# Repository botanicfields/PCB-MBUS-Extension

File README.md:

# PCB-MBUS-Extension
a Printed Circuit Board of M-Bus Extension for M5Stack

# M-Busエクステンション基板キット
M5Stackの外にM-Busモジュールを接続するエクステンション基板のキットです。M5Stack用BUSモジュールに取り付けて使用します。
- M5StackのLCDやボタンを使いながら、M-Busモジュールの試験や調整ができます。
- プロービング用のピンソケットからジャンパーワイヤーでM-Bus信号を観測できます。
- ボトムに出ていないM-Bus信号を観測できます。

## 委託販売（スイッチサイエンス）
https://www.switch-science.com/catalog/7371/

## 内容物
- プリント基板 ×1
- M-Busピンソケット(M5Stack純正品) ×1
- ピンソケット(一般用15ピン2列) ×1
- ピンソケット(一般用L型15ピン2列) ×1

※ M5Stack用BUSモジュールは付属しません。別途ご用意ください。

## ご注意
- 組み立てには、はんだ付け（表面実装を含む）が必要です。
- M-Bus信号へのノイズ混入により動作が不安定になる場合があります。信号には手を触れない様にしてください。
- M5Stack用BUSモジュールを含め基板パターンの電流容量が不足する可能性があります。GND, 5V, 3.3V, BAT, HPWRなど、必要に応じてディスクリートワイヤで補強してください。
- 取り扱い説明書はありません。

## 使用方法
- M5Stack用BUSモジュールについて、モジュール付属のL型ピンヘッダをはんだ付けし、モールド側面の開口部をカッター等で切り取ります。
- M5Stack用BUSモジュールに、組み立てたM-Busエクステンション基板を、**裏表が逆になるように取り付けます**。
- 本来、M5Stackの裏面側にあるM-Busモジュールが、エクステンション基板では表面を向きます。

## 使用例
RTCモジュールのCLKO信号を、M-Busエクステンション基板のGPIO36から取り出して周波数カウンタで観測しながら、RTCモジュールの水晶発振子のトリマを調整しています。M5StackのLCDも同時に見ることができます。

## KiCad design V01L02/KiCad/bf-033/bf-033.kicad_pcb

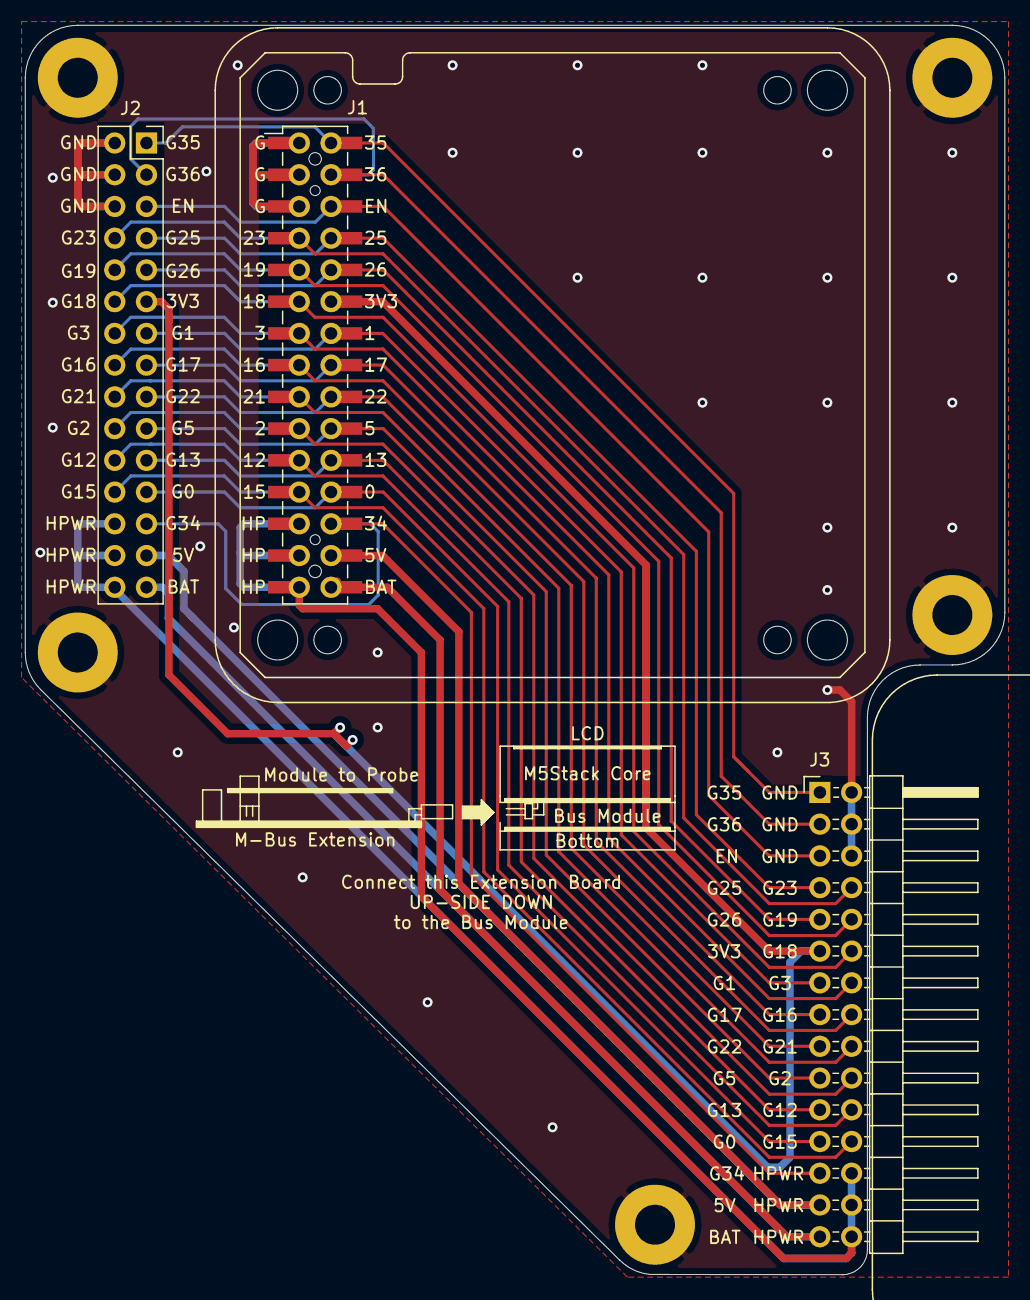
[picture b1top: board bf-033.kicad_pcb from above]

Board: 2 copper layers, 78.4 x 100.0 mm, 11 parts (0 on the bottom side), 26 nets.

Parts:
H1, H2, H3, H4: MountingHole; BF@MountingHole_3.2mm_M3
H5, H6, H7, H8: MountingHole; BF@MountingHole_2.2mm_M2
J1: M-BUS; BF@M5Stack_MBUS
J2: M-BUS; PinSocket_2x15_P2.54mm_Vertical
J3: M-BUS; PinHeader_2x15_P2.54mm_Horizontal

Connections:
+3V3: J1.11, J2.11, J3.11
+5V: J1.27, J2.27, J3.27
+BATT: J1.29, J2.29, J3.29
/EN: J1.5, J2.5, J3.5
/GPIO0: J1.23, J2.23, J3.23
/GPIO1: J1.13, J2.13, J3.13
/GPIO2: J1.20, J2.20, J3.20
/GPIO3: J1.14, J2.14, J3.14
/GPIO5: J1.19, J2.19, J3.19
/GPIO12: J1.22, J2.22, J3.22
/GPIO13: J1.21, J2.21, J3.21
/GPIO15: J1.24, J2.24, J3.24
/GPIO16: J1.16, J2.16, J3.16
/GPIO17: J1.15, J2.15, J3.15
/GPIO18: J1.12, J2.12, J3.12
/GPIO19: J1.10, J2.10, J3.10
/GPIO21: J1.18, J2.18, J3.18
/GPIO22: J1.17, J2.17, J3.17
/GPIO23: J1.8, J2.8, J3.8
/GPIO25: J1.7, J2.7, J3.7
/GPIO26: J1.9, J2.9, J3.9
/GPIO34: J1.25, J2.25, J3.25
/GPIO35: J1.1, J2.1, J3.1
/GPIO36: J1.3, J2.3, J3.3
GND: J1.2, J1.4, J1.6, J2.2, J2.4, J2.6, J3.2, J3.4, J3.6
VBUS: J1.26, J1.28, J1.30, J2.26, J2.28, J2.30, J3.26, J3.28, J3.30

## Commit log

2021-07-18 first upload

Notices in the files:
V01L02/KiCad/bf-033/bf-033.kicad_pcb:
Copyright 2021 BotanicFields, Inc.
